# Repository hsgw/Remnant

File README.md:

# Remnant

4x2 macro keyboard with attiny85 based digispark.

# Document
- [開発環境のインストール](doc/install_env_jp.md)
- [ビルドガイド（日本語）](doc/buildguide_jp.md)

# Needs
- Arduino IDE and Digispark
https://digistump.com/wiki/digispark/tutorials/connecting

- DigisparkKeyboardExtend library 
https://github.com/hsgw/DigisparkKeyboardExtend

# License
Digispark is licensed under CC BY-SA 3.0    http://creativecommons.org/licenses/by-sa/3.0/   
(c) Digistump   

Remnant is licensed under CC BY-SA 3.0    http://creativecommons.org/licenses/by-sa/3.0/   
(c) 2019, Takuya Urakawa, dm9records.com

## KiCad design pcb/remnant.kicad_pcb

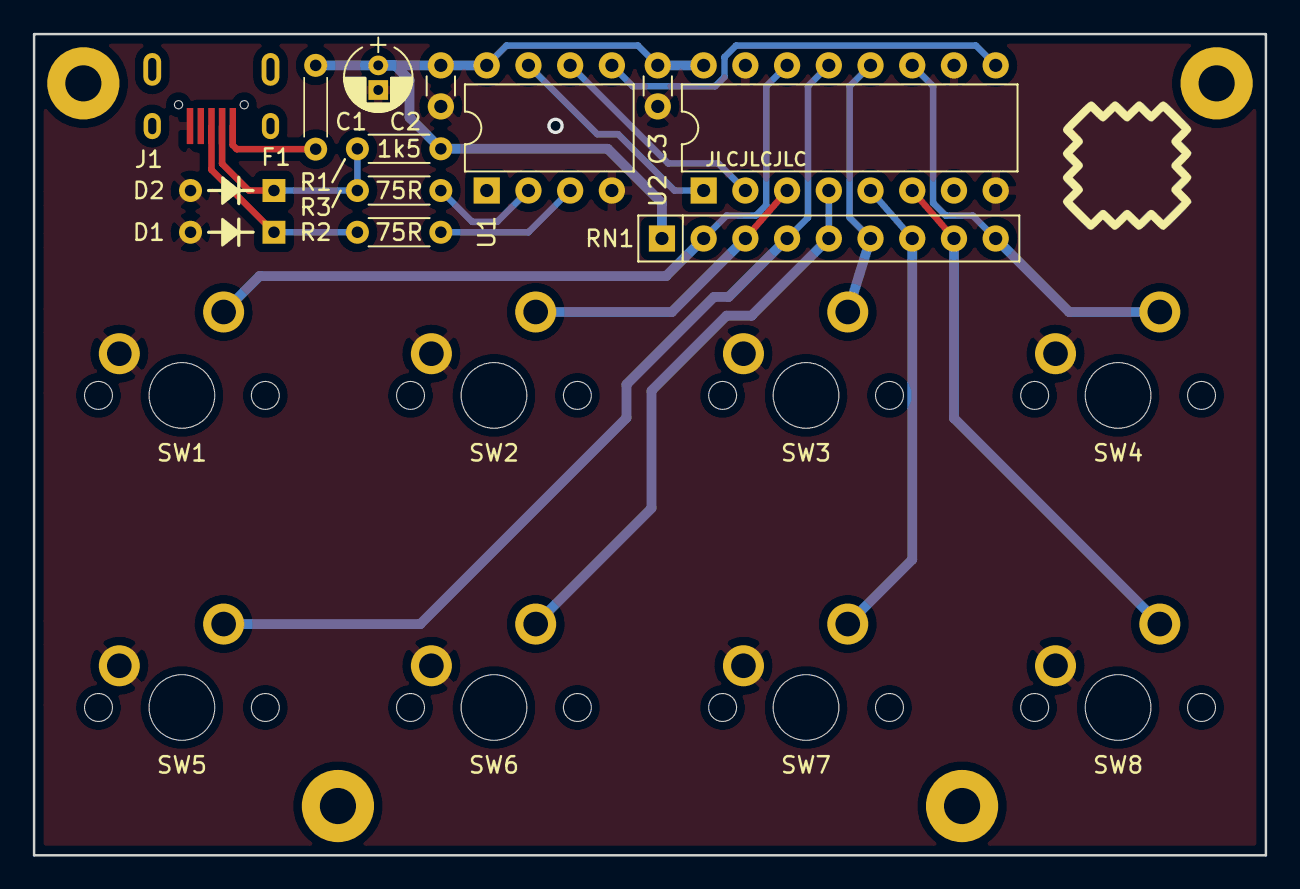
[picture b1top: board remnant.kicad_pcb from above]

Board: 2 copper layers, 75.0 x 50.0 mm, 25 parts (0 on the bottom side), 18 nets.

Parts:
C1: 10u; CP_Radial_D4.0mm_P1.50mm
C2, C3: 100n; C_Disc_D3.0mm_W1.6mm_P2.50mm
D1, D2: 3.6V; D_DO-35_SOD27_P5.08mm_Horizontal
F1: 100mA; polyfuse_5.1mm
H1, H2, H3, H4: MountingHole; MountingHole_2.2mm_M2_Pad
J1: USB_OTG; USB-microB-LCSC-U-F-M5DD-W-2
R1: 1k5; R_Axial_DIN0204_L3.6mm_D1.6mm_P5.08mm_Horizontal
R2, R3: 75R; R_Axial_DIN0204_L3.6mm_D1.6mm_P5.08mm_Horizontal
RN1: R_Network08; R_Array_SIP9
SW1, SW2, SW3, SW4, SW5, SW6, SW7, SW8: MX; SW_Cherry_MX1A_1.00u_PCB
U1: ATTINY85-20PU; DIP-8_W7.62mm
U2: 74LS165; DIP-16_W7.62mm

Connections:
+5V: C1.1, C2.1, C3.1, F1.1, R1.2, RN1.1, U1.8, U2.16
/SW1: RN1.2, SW1.2, U2.14
/SW2: RN1.3, SW2.2, U2.3
/SW3: RN1.6, SW3.2, U2.12
/SW4: RN1.9, SW4.2, U2.11
/SW5: RN1.4, SW5.2, U2.13
/SW6: RN1.5, SW6.2, U2.4
/SW7: RN1.7, SW7.2, U2.5
/SW8: RN1.8, SW8.2, U2.6
/USB_D+: R2.1, U1.3
/USB_D-: R3.1, U1.2
GND: C1.2, C2.2, C3.2, D1.2, D2.2, J1.5, SW1.1, SW2.1, SW3.1, SW4.1, SW5.1, SW6.1, SW7.1, SW8.1, U1.4, U2.8, U2.10, U2.15
unnamed: D1.1, J1.3, R2.2
unnamed: D2.1, J1.2, R1.1, R3.2
unnamed: F1.2, J1.1
unnamed: U1.5, U2.9
unnamed: U1.6, U2.2
unnamed: U1.7, U2.1

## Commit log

2019-05-22 1st commit
2019-05-22 add image
2019-05-22 add arduino src
2019-07-04 update gitignore
2019-07-04 add buildguide_jp.md
2019-07-07 fix keymap
